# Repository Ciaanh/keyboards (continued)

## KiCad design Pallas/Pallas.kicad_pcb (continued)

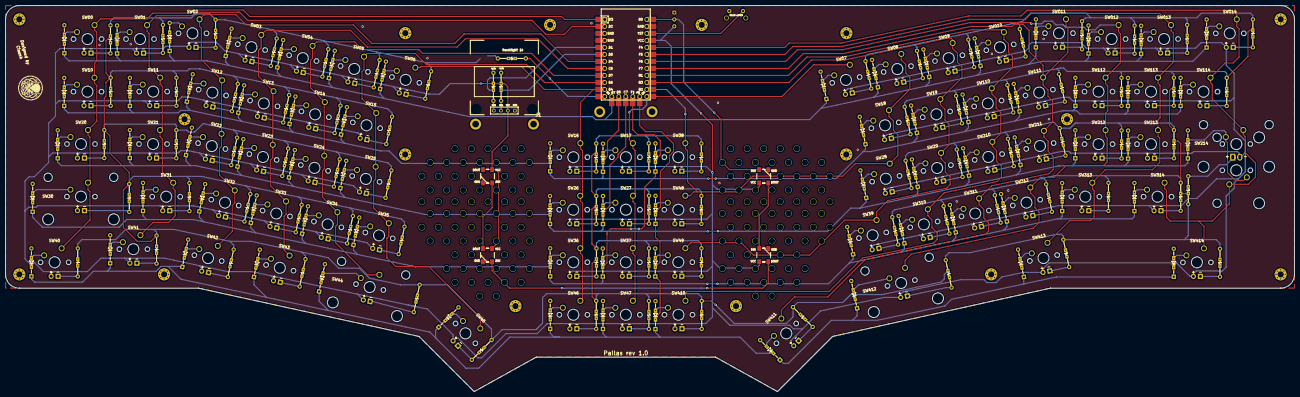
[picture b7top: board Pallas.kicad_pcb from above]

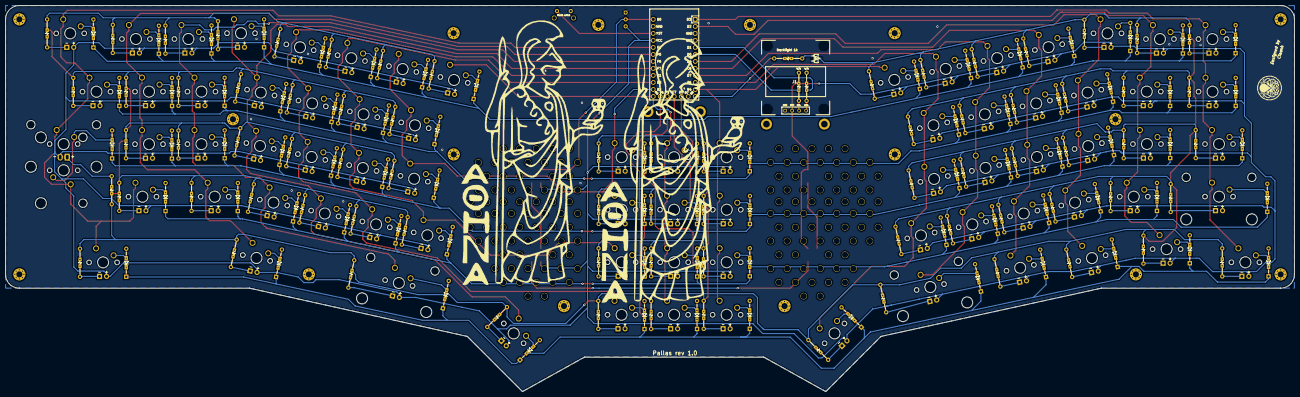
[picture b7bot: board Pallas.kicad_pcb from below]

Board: 2 copper layers, 467.5 x 140.0 mm, 262 parts (3 on the bottom side), 182 nets.

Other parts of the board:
DecorationHoleTop1, DecorationHoleTop2: DecorationHole
LogoBase1: LOGO; athena
LogoBaseMiddleTop: LOGO; Ciaanh_signature
LogoMiddle2: LOGO; athena
MountBaseMiddleTop0, MountBaseMiddleTop2, MountBaseMiddleTop3, MountBaseMiddleTop4, MountBaseMiddleTop5, MountBaseMiddleTop6, MountBaseMiddleTop7, MountBaseMiddleTop8, MountBaseMiddleTop9, MountBaseMiddleTop10, MountBaseMiddleTop11, MountBaseMiddleTop12, MountBaseMiddleTop13, MountBaseMiddleTop14, MountBaseMiddleTop15, MountBaseMiddleTop15#2: MountingHole; MountingHole_2.2mm_M2_Pad_Via
MountForMiddle1: HOLE; MountingHole_2.4mm_M2_Pad
MountMiddle1, MountMiddle2, MountMiddle3: HOLE; MountingHole_2.4mm_M2_Pad

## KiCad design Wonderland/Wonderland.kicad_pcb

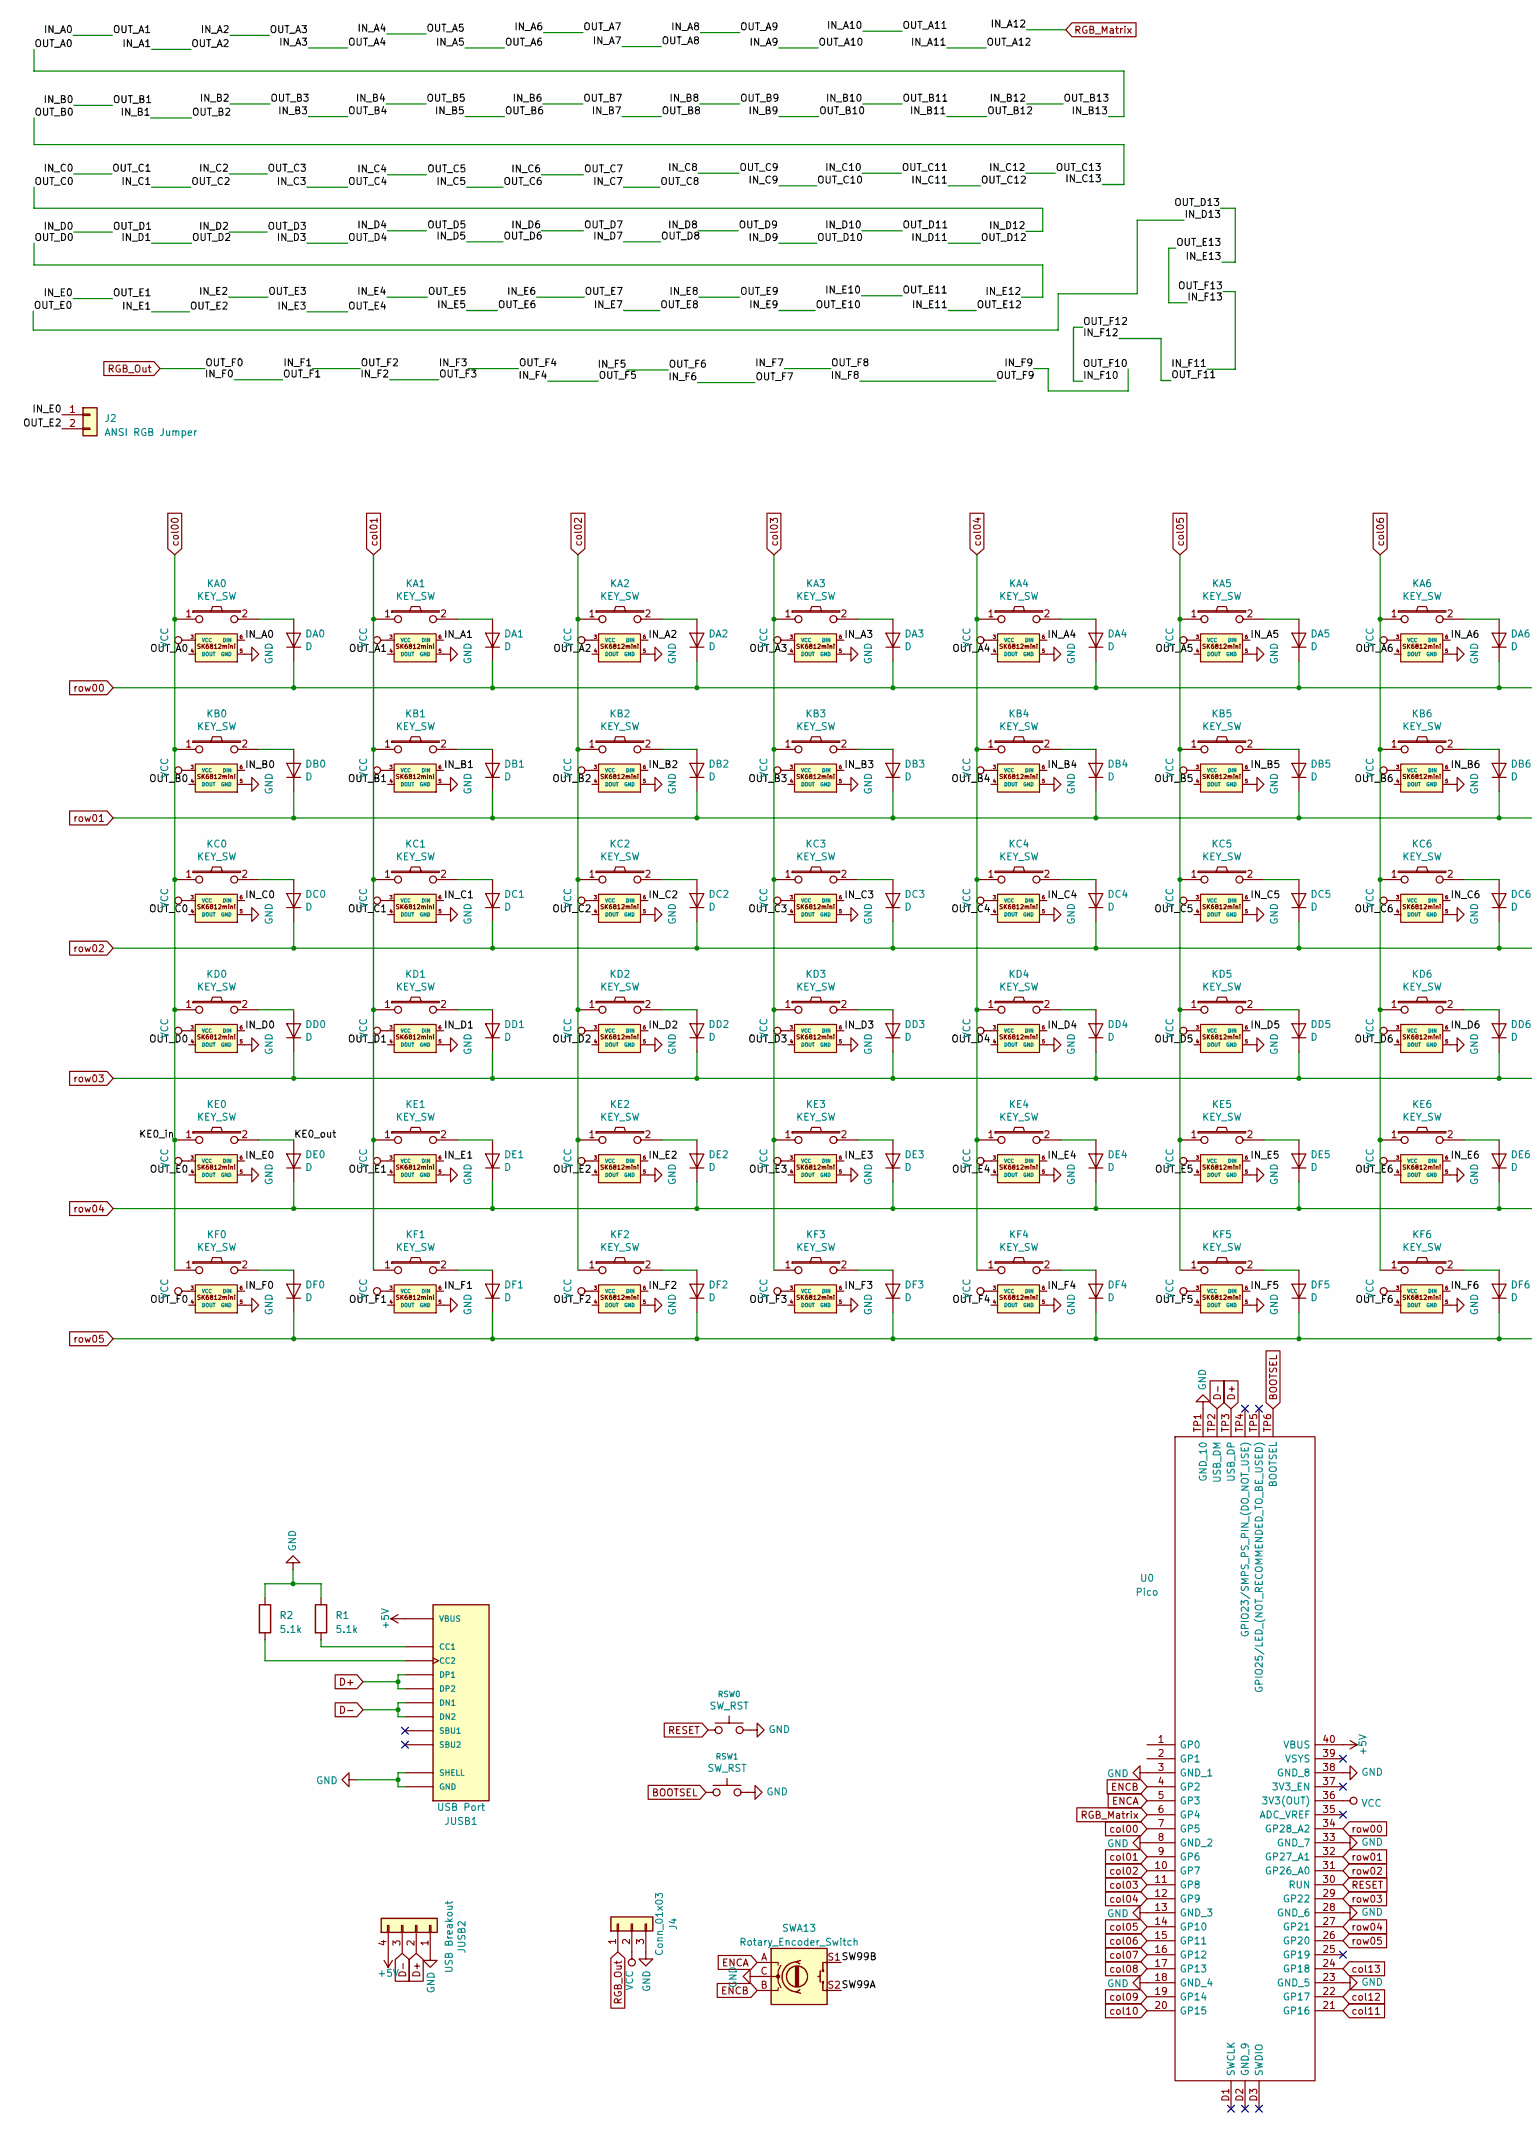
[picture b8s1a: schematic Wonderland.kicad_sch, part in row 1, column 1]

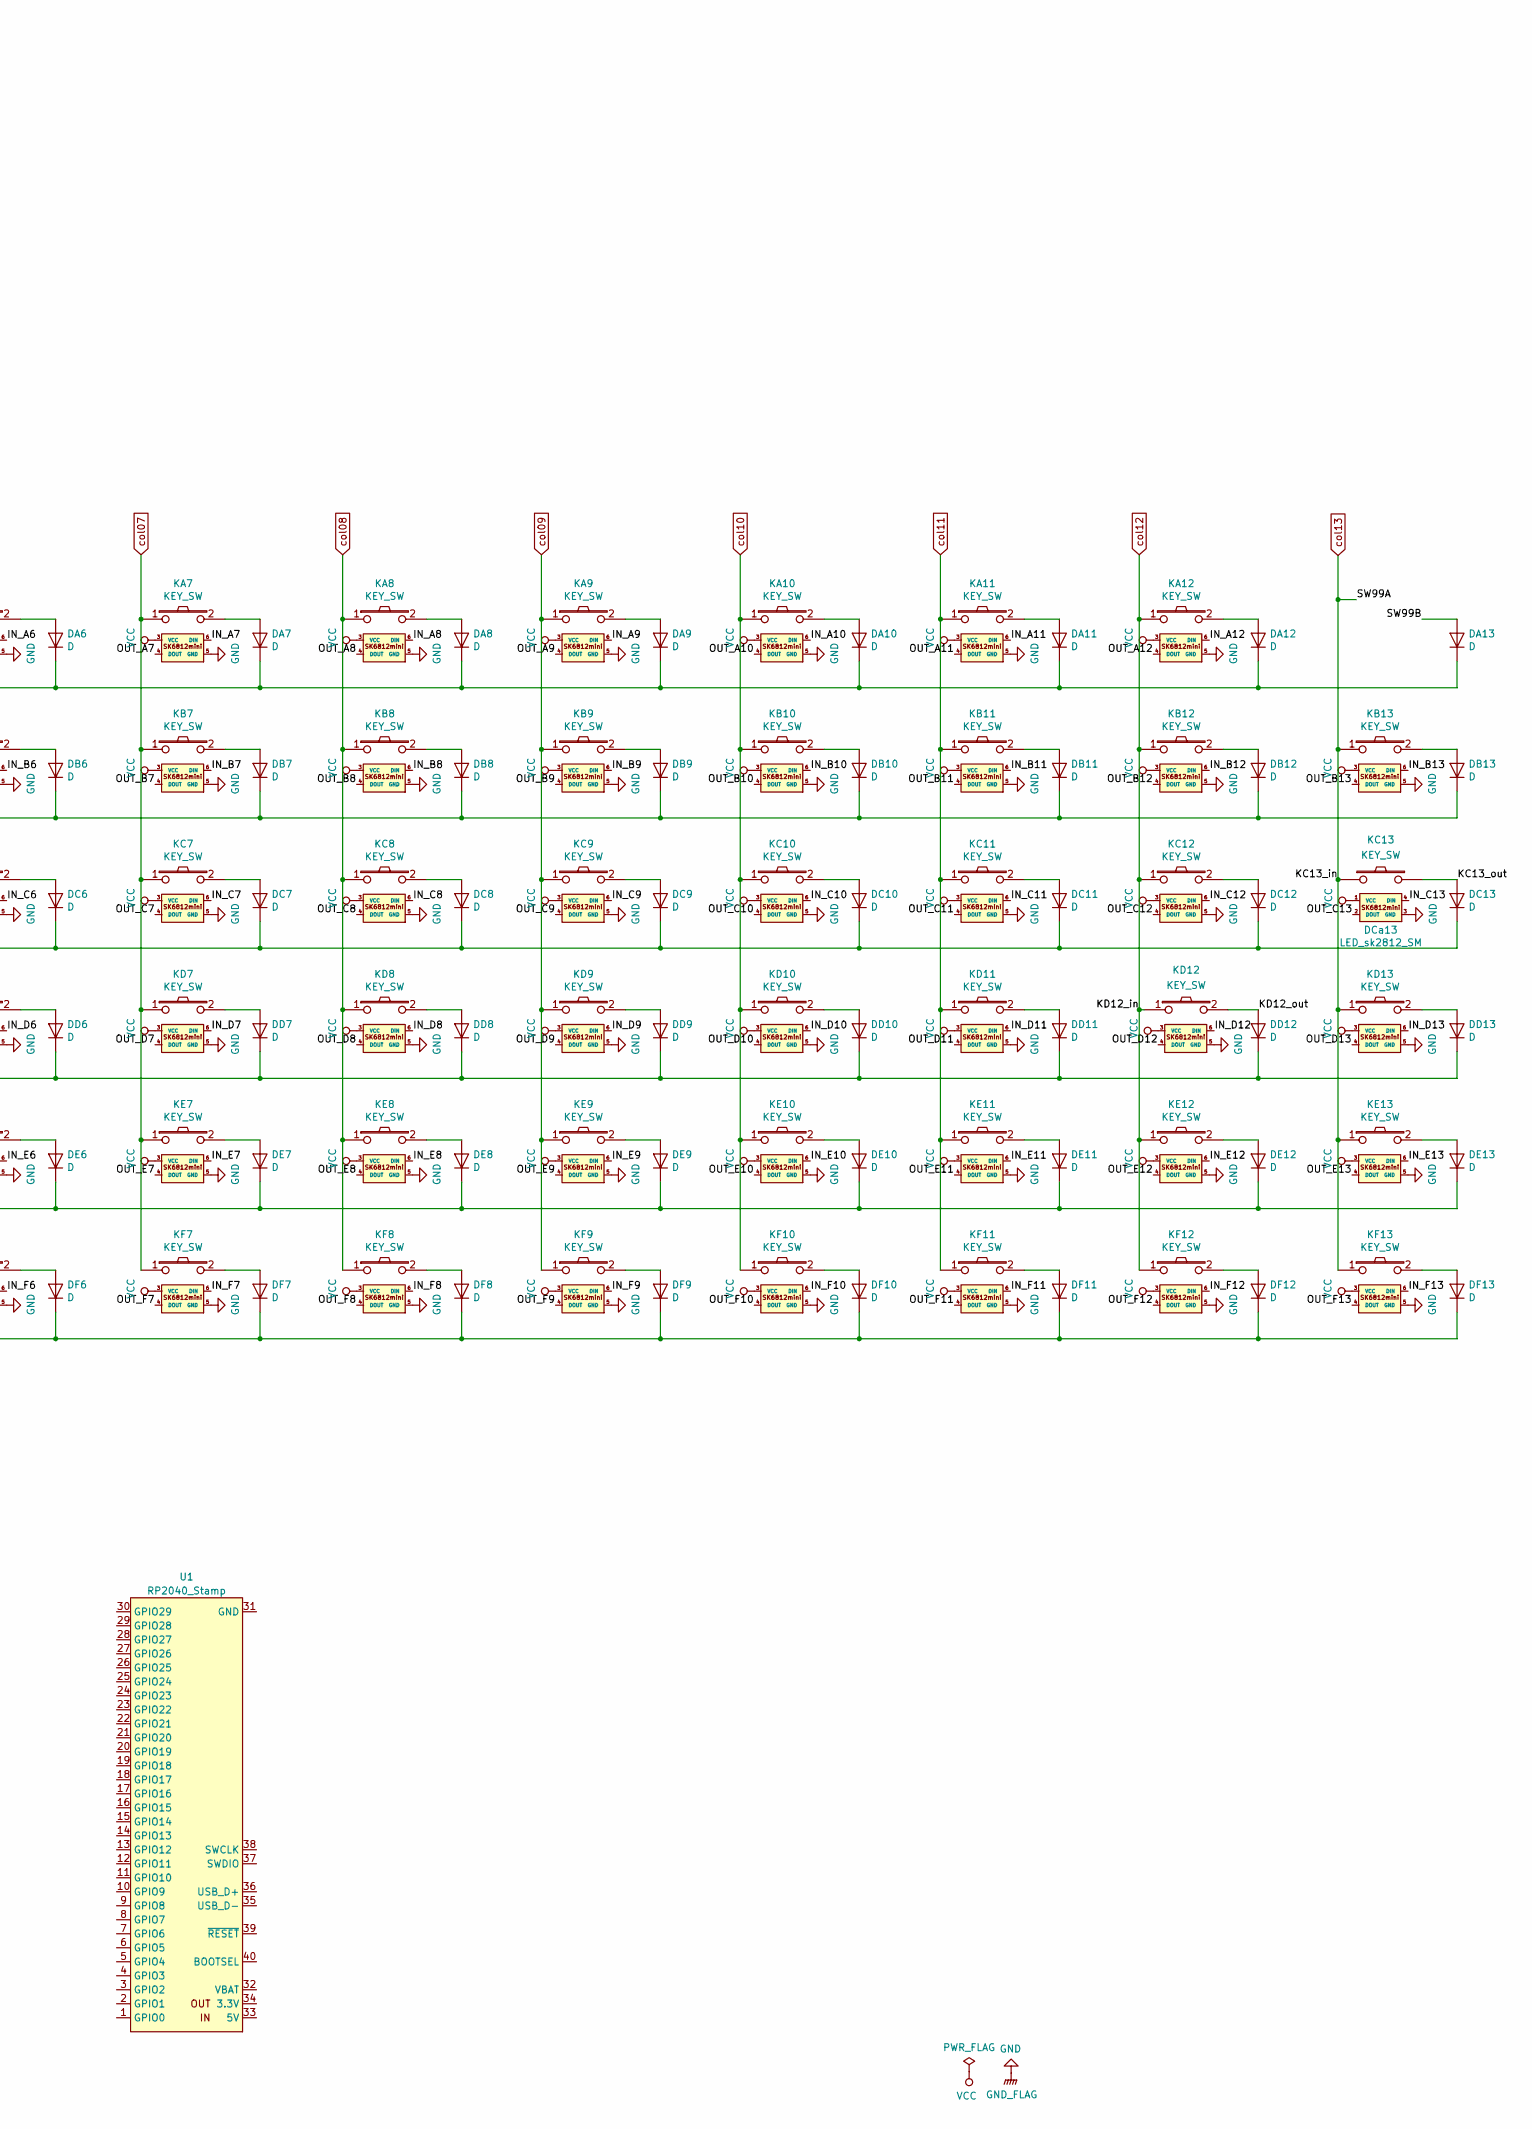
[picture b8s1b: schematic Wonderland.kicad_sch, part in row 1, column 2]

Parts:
DA0, DA1, DA2, DA3, DA4, DA5, DA6, DA7, DA8, DA9, DA10, DA11, DA12, DA13: D; Diode_THT
DB0, DB1, DB2, DB3, DB4, DB5, DB6, DB7, DB8, DB9, DB10, DB11, DB12, DB13: D; Diode_THT
DC0, DC1, DC2, DC3, DC4, DC5, DC6, DC7, DC8, DC9, DC10, DC11, DC12, DC13: D; Diode_THT
DCa13: LED_sk2812_SM; SK6812-MINI-E_back
DD0, DD1, DD2, DD3, DD4, DD5, DD6, DD7, DD8, DD9, DD10, DD11, DD12, DD13: D; Diode_THT
DE0, DE1, DE2, DE3, DE4, DE5, DE6, DE7, DE8, DE9, DE10, DE11, DE12, DE13: D; Diode_THT
DF0, DF1, DF2, DF3, DF4, DF5, DF6, DF7, DF8, DF9, DF10, DF11, DF12, DF13: D; Diode_THT
J2: ANSI RGB Jumper; SolderJumper
J4: Conn_01x03; conn_3pins
JUSB1: USB Port; GCT_USB4085-GF-A_REVA4; PARTREV A4
JUSB2: USB Breakout; conn_4pins
KA0, KA1, KA2, KA3, KA4, KA5, KA6, KA7, KA8, KA9, KA10, KA11, KA12: KEY_SW; SW_Cherry_MX_1.00u_SK6812MINI-E_Hotswap
KB0, KB1, KB2, KB3, KB4, KB5, KB6, KB7, KB8, KB9, KB10, KB11, KB12: KEY_SW; SW_Cherry_MX_1.00u_SK6812MINI-E_Hotswap
KB13: KEY_SW; SW_Cherry_MX_2.00u_SK6812MINI-E_Hotswap
KC0: KEY_SW; SW_Cherry_MX_1.50u_SK6812MINI-E_Hotswap
KC1, KC2, KC3, KC4, KC5, KC6, KC7, KC8, KC9, KC10, KC11, KC12: KEY_SW; SW_Cherry_MX_1.00u_SK6812MINI-E_Hotswap
KC13: KEY_SW; SW_Cherry_MX_2.25u_ISO_Hotswap
KD0: KEY_SW; SW_Cherry_MX_1.75u_SK6812MINI-E_Hotswap
KD1, KD2, KD3, KD4, KD5, KD6, KD7, KD8, KD9, KD10, KD11, KD12, KD13: KEY_SW; SW_Cherry_MX_1.00u_SK6812MINI-E_Hotswap
KE0: KEY_SW; SW_Cherry_MX_1.25u_SK6812MINI-E_Hotswap
KE1, KE2, KE3, KE4, KE5, KE6, KE7, KE8, KE9, KE10, KE11, KE13: KEY_SW; SW_Cherry_MX_1.00u_SK6812MINI-E_Hotswap
KE12: KEY_SW; SW_Cherry_MX_1.75u_SK6812MINI-E_Hotswap
KF0, KF1, KF2, KF3, KF6, KF7, KF8, KF9, KF10, KF11, KF12, KF13: KEY_SW; SW_Cherry_MX_1.00u_SK6812MINI-E_Hotswap
KF4: KEY_SW; SW_Cherry_MX_2.25u_SK6812MINI-E_Hotswap_Reversed
KF5: KEY_SW; SW_Cherry_MX_2.75u_SK6812MINI-E_Hotswap_Reversed
R1, R2: 5.1k; Resistors_THT
RSW0, RSW1: SW_RST
SWA13: Rotary_Encoder_Switch; RotaryEncoder_EC11-Switch_Horizontal_H15mm
U0: Pico; RPi_Pico_TH; Manufacturer_Part_Number PICO
U1: RP2040_Stamp; RP2040_Stamp_THT

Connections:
+5V: JUSB1.A4 (VBUS), JUSB1.A9 (VBUS), JUSB1.B4 (VBUS), JUSB1.B9 (VBUS), JUSB2.4, U0.40 (VBUS)
/IN_A0: KA0.6 (DIN), KA1.4 (DOUT)
/IN_A1: KA1.6 (DIN), KA2.4 (DOUT)
/IN_A2: KA2.6 (DIN), KA3.4 (DOUT)
/IN_A3: KA3.6 (DIN), KA4.4 (DOUT)
/IN_A4: KA4.6 (DIN), KA5.4 (DOUT)
/IN_A5: KA5.6 (DIN), KA6.4 (DOUT)
/IN_A6: KA6.6 (DIN), KA7.4 (DOUT)
/IN_A7: KA7.6 (DIN), KA8.4 (DOUT)
/IN_A8: KA8.6 (DIN), KA9.4 (DOUT)
/IN_A9: KA9.6 (DIN), KA10.4 (DOUT)
/IN_A10: KA10.6 (DIN), KA11.4 (DOUT)
/IN_A11: KA11.6 (DIN), KA12.4 (DOUT)
/IN_B0: KB0.6 (DIN), KB1.4 (DOUT)
/IN_B1: KB1.6 (DIN), KB2.4 (DOUT)
/IN_B2: KB2.6 (DIN), KB3.4 (DOUT)
/IN_B3: KB3.6 (DIN), KB4.4 (DOUT)
/IN_B4: KB4.6 (DIN), KB5.4 (DOUT)
/IN_B5: KB5.6 (DIN), KB6.4 (DOUT)
/IN_B6: KB6.6 (DIN), KB7.4 (DOUT)
/IN_B7: KB7.6 (DIN), KB8.4 (DOUT)
/IN_B8: KB8.6 (DIN), KB9.4 (DOUT)
/IN_B9: KB9.6 (DIN), KB10.4 (DOUT)
/IN_B10: KB10.6 (DIN), KB11.4 (DOUT)
/IN_B11: KB11.6 (DIN), KB12.4 (DOUT)
/IN_B12: KB12.6 (DIN), KB13.4 (DOUT)
/IN_B13: KA0.4 (DOUT), KB13.6 (DIN)
/IN_C0: KC0.6 (DIN), KC1.4 (DOUT)
/IN_C1: KC1.6 (DIN), KC2.4 (DOUT)
/IN_C2: KC2.6 (DIN), KC3.4 (DOUT)
/IN_C3: KC3.6 (DIN), KC4.4 (DOUT)
/IN_C4: KC4.6 (DIN), KC5.4 (DOUT)
/IN_C5: KC5.6 (DIN), KC6.4 (DOUT)
/IN_C6: KC6.6 (DIN), KC7.4 (DOUT)
/IN_C7: KC7.6 (DIN), KC8.4 (DOUT)
/IN_C8: KC8.6 (DIN), KC9.4 (DOUT)
/IN_C9: KC9.6 (DIN), KC10.4 (DOUT)
/IN_C10: KC10.6 (DIN), KC11.4 (DOUT)
/IN_C11: KC11.6 (DIN), KC12.4 (DOUT)
/IN_C12: DCa13.2 (DOUT), KC12.6 (DIN)
/IN_C13: DCa13.4 (DIN), KB0.4 (DOUT)
/IN_D0: KD0.6 (DIN), KD1.4 (DOUT)
/IN_D1: KD1.6 (DIN), KD2.4 (DOUT)
/IN_D2: KD2.6 (DIN), KD3.4 (DOUT)
/IN_D3: KD3.6 (DIN), KD4.4 (DOUT)
/IN_D4: KD4.6 (DIN), KD5.4 (DOUT)
/IN_D5: KD5.6 (DIN), KD6.4 (DOUT)
/IN_D6: KD6.6 (DIN), KD7.4 (DOUT)
/IN_D7: KD7.6 (DIN), KD8.4 (DOUT)
/IN_D8: KD8.6 (DIN), KD9.4 (DOUT)
/IN_D9: KD9.6 (DIN), KD10.4 (DOUT)
/IN_D10: KD10.6 (DIN), KD11.4 (DOUT)
/IN_D11: KD11.6 (DIN), KD12.4 (DOUT)
/IN_D12: KC0.4 (DOUT), KD12.6 (DIN)
/IN_D13: KD13.6 (DIN), KE0.4 (DOUT)
/IN_E0: J2.1, KE0.6 (DIN), KE1.4 (DOUT)
/IN_E1: J2.2, KE1.6 (DIN), KE2.4 (DOUT)
/IN_E2: KE2.6 (DIN), KE3.4 (DOUT)
/IN_E3: KE3.6 (DIN), KE4.4 (DOUT)
/IN_E4: KE4.6 (DIN), KE5.4 (DOUT)
/IN_E5: KE5.6 (DIN), KE6.4 (DOUT)
/IN_E6: KE6.6 (DIN), KE7.4 (DOUT)
/IN_E7: KE7.6 (DIN), KE8.4 (DOUT)
/IN_E8: KE8.6 (DIN), KE9.4 (DOUT)
/IN_E9: KE9.6 (DIN), KE10.4 (DOUT)
/IN_E10: KE10.6 (DIN), KE11.4 (DOUT)
/IN_E11: KE11.6 (DIN), KE12.4 (DOUT)
/IN_E12: KD0.4 (DOUT), KE12.6 (DIN)
/IN_E13: KD13.4 (DOUT), KE13.6 (DIN)
/IN_F0: KF0.6 (DIN), KF1.4 (DOUT)
/IN_F1: KF1.6 (DIN), KF2.4 (DOUT)
/IN_F2: KF2.6 (DIN), KF3.4 (DOUT)
/IN_F3: KF3.6 (DIN), KF4.4 (DOUT)
/IN_F4: KF4.6 (DIN), KF5.4 (DOUT)
/IN_F5: KF5.6 (DIN), KF6.4 (DOUT)
/IN_F6: KF6.6 (DIN), KF7.4 (DOUT)
/IN_F7: KF7.6 (DIN), KF8.4 (DOUT)
/IN_F8: KF8.6 (DIN), KF9.4 (DOUT)
/IN_F9: KF9.6 (DIN), KF10.4 (DOUT)
/IN_F10: KF10.6 (DIN), KF12.4 (DOUT)
/IN_F11: KF11.6 (DIN), KF13.4 (DOUT)
/IN_F12: KF11.4 (DOUT), KF12.6 (DIN)
/IN_F13: KE13.4 (DOUT), KF13.6 (DIN)
/KC13_out: DC13.2 (A), KC13.2
/KD12_out: DD12.2 (A), KD12.2
/KE0_out: DE0.2 (A), KE0.2
/SW99B: DA13.2 (A), SWA13.S1
BOOTSEL: RSW1.1, U0.TP6 (BOOTSEL)
D+: JUSB1.A6 (DP1), JUSB1.B6 (DP2), JUSB2.2, U0.TP3 (USB_DP)
D-: JUSB1.A7 (DN1), JUSB1.B7 (DN2), JUSB2.3, U0.TP2 (USB_DM)
ENCA: SWA13.A, U0.5 (GP3)
ENCB: SWA13.B, U0.4 (GP2)
GND: DCa13.3 (GND), J4.3, JUSB1.A1 (GND), JUSB1.A12 (GND), JUSB1.B1 (GND), JUSB1.B12 (GND), JUSB1.P1 (SHELL), JUSB1.P2 (SHELL), JUSB1.P3 (SHELL), JUSB1.P4 (SHELL), JUSB2.1, KA0.5 (GND), KA1.5 (GND), KA2.5 (GND), KA3.5 (GND), KA4.5 (GND), KA5.5 (GND), KA6.5 (GND), KA7.5 (GND), KA8.5 (GND), KA9.5 (GND), KA10.5 (GND), KA11.5 (GND), KA12.5 (GND), KB0.5 (GND), KB1.5 (GND), KB2.5 (GND), KB3.5 (GND), KB4.5 (GND), KB5.5 (GND), KB6.5 (GND), KB7.5 (GND), KB8.5 (GND), KB9.5 (GND), KB10.5 (GND), KB11.5 (GND), KB12.5 (GND), KB13.5 (GND), KC0.5 (GND), KC1.5 (GND), KC2.5 (GND), KC3.5 (GND), KC4.5 (GND), KC5.5 (GND), KC6.5 (GND), KC7.5 (GND), KC8.5 (GND), KC9.5 (GND), KC10.5 (GND), KC11.5 (GND), KC12.5 (GND), KD0.5 (GND), KD1.5 (GND), KD2.5 (GND), KD3.5 (GND), KD4.5 (GND), KD5.5 (GND), KD6.5 (GND), KD7.5 (GND), KD8.5 (GND), KD9.5 (GND), KD10.5 (GND), KD11.5 (GND), KD12.5 (GND), KD13.5 (GND), KE0.5 (GND), KE1.5 (GND), KE2.5 (GND), KE3.5 (GND), KE4.5 (GND), KE5.5 (GND), KE6.5 (GND), KE7.5 (GND), KE8.5 (GND), KE9.5 (GND), KE10.5 (GND), KE11.5 (GND), KE12.5 (GND), KE13.5 (GND), KF0.5 (GND), KF1.5 (GND), KF2.5 (GND), KF3.5 (GND), KF4.5 (GND), KF5.5 (GND), KF6.5 (GND), KF7.5 (GND), KF8.5 (GND), KF9.5 (GND), KF10.5 (GND), KF11.5 (GND), KF12.5 (GND), KF13.5 (GND), R1.1, R2.1, RSW0.2, RSW1.2, SWA13.C, U0.3 (GND_1), U0.8 (GND_2), U0.13 (GND_3), U0.18 (GND_4), U0.23 (GND_5), U0.28 (GND_6), U0.33 (GND_7), U0.38 (GND_8), U0.TP1 (GND_10)
unnamed: DA0.2 (A), KA0.2
unnamed: DA1.2 (A), KA1.2
unnamed: DA2.2 (A), KA2.2
unnamed: DA3.2 (A), KA3.2
unnamed: DA4.2 (A), KA4.2
unnamed: DA5.2 (A), KA5.2
unnamed: DA6.2 (A), KA6.2
unnamed: DA7.2 (A), KA7.2
unnamed: DA8.2 (A), KA8.2
unnamed: DA9.2 (A), KA9.2
unnamed: DA10.2 (A), KA10.2
unnamed: DA11.2 (A), KA11.2
unnamed: DA12.2 (A), KA12.2
unnamed: DB0.2 (A), KB0.2
unnamed: DB1.2 (A), KB1.2
unnamed: DB2.2 (A), KB2.2
unnamed: DB3.2 (A), KB3.2
unnamed: DB4.2 (A), KB4.2
unnamed: DB5.2 (A), KB5.2
unnamed: DB6.2 (A), KB6.2
unnamed: DB7.2 (A), KB7.2
unnamed: DB8.2 (A), KB8.2
unnamed: DB9.2 (A), KB9.2
unnamed: DB10.2 (A), KB10.2
unnamed: DB11.2 (A), KB11.2
unnamed: DB12.2 (A), KB12.2
unnamed: DB13.2 (A), KB13.2
unnamed: DC0.2 (A), KC0.2
unnamed: DC1.2 (A), KC1.2
unnamed: DC2.2 (A), KC2.2
unnamed: DC3.2 (A), KC3.2
unnamed: DC4.2 (A), KC4.2
unnamed: DC5.2 (A), KC5.2
unnamed: DC6.2 (A), KC6.2
unnamed: DC7.2 (A), KC7.2
unnamed: DC8.2 (A), KC8.2
unnamed: DC9.2 (A), KC9.2
unnamed: DC10.2 (A), KC10.2
unnamed: DC11.2 (A), KC11.2
unnamed: DC12.2 (A), KC12.2
unnamed: DD0.2 (A), KD0.2
unnamed: DD1.2 (A), KD1.2
unnamed: DD2.2 (A), KD2.2
unnamed: DD3.2 (A), KD3.2
unnamed: DD4.2 (A), KD4.2
unnamed: DD5.2 (A), KD5.2
unnamed: DD6.2 (A), KD6.2
unnamed: DD7.2 (A), KD7.2
unnamed: DD8.2 (A), KD8.2
unnamed: DD9.2 (A), KD9.2
unnamed: DD10.2 (A), KD10.2
unnamed: DD11.2 (A), KD11.2
unnamed: DD13.2 (A), KD13.2
unnamed: DE1.2 (A), KE1.2
unnamed: DE2.2 (A), KE2.2
unnamed: DE3.2 (A), KE3.2
unnamed: DE4.2 (A), KE4.2
unnamed: DE5.2 (A), KE5.2
unnamed: DE6.2 (A), KE6.2
unnamed: DE7.2 (A), KE7.2
unnamed: DE8.2 (A), KE8.2
unnamed: DE9.2 (A), KE9.2
unnamed: DE10.2 (A), KE10.2
unnamed: DE11.2 (A), KE11.2
unnamed: DE12.2 (A), KE12.2
unnamed: DE13.2 (A), KE13.2
unnamed: DF0.2 (A), KF0.2
unnamed: DF1.2 (A), KF1.2
unnamed: DF2.2 (A), KF2.2
unnamed: DF3.2 (A), KF3.2
unnamed: DF4.2 (A), KF4.2
unnamed: DF5.2 (A), KF5.2
unnamed: DF6.2 (A), KF6.2
unnamed: DF7.2 (A), KF7.2
unnamed: DF8.2 (A), KF8.2
unnamed: DF9.2 (A), KF9.2
unnamed: DF10.2 (A), KF10.2
unnamed: DF11.2 (A), KF11.2
unnamed: DF12.2 (A), KF12.2
unnamed: DF13.2 (A), KF13.2
unnamed: JUSB1.A5 (CC1), R1.2
unnamed: JUSB1.B5 (CC2), R2.2
RESET: RSW0.1, U0.30 (RUN)
RGB_Matrix: KA12.6 (DIN), U0.6 (GP4)
RGB_Out: J4.1, KF0.4 (DOUT)
VCC: DCa13.1 (VCC), J4.2, KA0.3 (VCC), KA1.3 (VCC), KA2.3 (VCC), KA3.3 (VCC), KA4.3 (VCC), KA5.3 (VCC), KA6.3 (VCC), KA7.3 (VCC), KA8.3 (VCC), KA9.3 (VCC), KA10.3 (VCC), KA11.3 (VCC), KA12.3 (VCC), KB0.3 (VCC), KB1.3 (VCC), KB2.3 (VCC), KB3.3 (VCC), KB4.3 (VCC), KB5.3 (VCC), KB6.3 (VCC), KB7.3 (VCC), KB8.3 (VCC), KB9.3 (VCC), KB10.3 (VCC), KB11.3 (VCC), KB12.3 (VCC), KB13.3 (VCC), KC0.3 (VCC), KC1.3 (VCC), KC2.3 (VCC), KC3.3 (VCC), KC4.3 (VCC), KC5.3 (VCC), KC6.3 (VCC), KC7.3 (VCC), KC8.3 (VCC), KC9.3 (VCC), KC10.3 (VCC), KC11.3 (VCC), KC12.3 (VCC), KD0.3 (VCC), KD1.3 (VCC), KD2.3 (VCC), KD3.3 (VCC), KD4.3 (VCC), KD5.3 (VCC), KD6.3 (VCC), KD7.3 (VCC), KD8.3 (VCC), KD9.3 (VCC), KD10.3 (VCC), KD11.3 (VCC), KD12.3 (VCC), KD13.3 (VCC), KE0.3 (VCC), KE1.3 (VCC), KE2.3 (VCC), KE3.3 (VCC), KE4.3 (VCC), KE5.3 (VCC), KE6.3 (VCC), KE7.3 (VCC), KE8.3 (VCC), KE9.3 (VCC), KE10.3 (VCC), KE11.3 (VCC), KE12.3 (VCC), KE13.3 (VCC), KF0.3 (VCC), KF1.3 (VCC), KF2.3 (VCC), KF3.3 (VCC), KF4.3 (VCC), KF5.3 (VCC), KF6.3 (VCC), KF7.3 (VCC), KF8.3 (VCC), KF9.3 (VCC), KF10.3 (VCC), KF11.3 (VCC), KF12.3 (VCC), KF13.3 (VCC), U0.36 (3V3(OUT))
col00: KA0.1, KB0.1, KC0.1, KD0.1, KE0.1, KF0.1, U0.7 (GP5)
col01: KA1.1, KB1.1, KC1.1, KD1.1, KE1.1, KF1.1, U0.9 (GP6)
col02: KA2.1, KB2.1, KC2.1, KD2.1, KE2.1, KF2.1, U0.10 (GP7)
col03: KA3.1, KB3.1, KC3.1, KD3.1, KE3.1, KF3.1, U0.11 (GP8)
col04: KA4.1, KB4.1, KC4.1, KD4.1, KE4.1, KF4.1, U0.12 (GP9)
col05: KA5.1, KB5.1, KC5.1, KD5.1, KE5.1, KF5.1, U0.14 (GP10)
col06: KA6.1, KB6.1, KC6.1, KD6.1, KE6.1, KF6.1, U0.15 (GP11)
col07: KA7.1, KB7.1, KC7.1, KD7.1, KE7.1, KF7.1, U0.16 (GP12)
col08: KA8.1, KB8.1, KC8.1, KD8.1, KE8.1, KF8.1, U0.17 (GP13)
col09: KA9.1, KB9.1, KC9.1, KD9.1, KE9.1, KF9.1, U0.19 (GP14)
col10: KA10.1, KB10.1, KC10.1, KD10.1, KE10.1, KF10.1, U0.20 (GP15)
col11: KA11.1, KB11.1, KC11.1, KD11.1, KE11.1, KF11.1, U0.21 (GP16)
col12: KA12.1, KB12.1, KC12.1, KD12.1, KE12.1, KF12.1, U0.22 (GP17)
col13: KB13.1, KC13.1, KD13.1, KE13.1, KF13.1, SWA13.S2, U0.24 (GP18)
row00: DA0.1 (K), DA1.1 (K), DA2.1 (K), DA3.1 (K), DA4.1 (K), DA5.1 (K), DA6.1 (K), DA7.1 (K), DA8.1 (K), DA9.1 (K), DA10.1 (K), DA11.1 (K), DA12.1 (K), DA13.1 (K), U0.34 (GP28_A2)
row01: DB0.1 (K), DB1.1 (K), DB2.1 (K), DB3.1 (K), DB4.1 (K), DB5.1 (K), DB6.1 (K), DB7.1 (K), DB8.1 (K), DB9.1 (K), DB10.1 (K), DB11.1 (K), DB12.1 (K), DB13.1 (K), U0.32 (GP27_A1)
row02: DC0.1 (K), DC1.1 (K), DC2.1 (K), DC3.1 (K), DC4.1 (K), DC5.1 (K), DC6.1 (K), DC7.1 (K), DC8.1 (K), DC9.1 (K), DC10.1 (K), DC11.1 (K), DC12.1 (K), DC13.1 (K), U0.31 (GP26_A0)
row03: DD0.1 (K), DD1.1 (K), DD2.1 (K), DD3.1 (K), DD4.1 (K), DD5.1 (K), DD6.1 (K), DD7.1 (K), DD8.1 (K), DD9.1 (K), DD10.1 (K), DD11.1 (K), DD12.1 (K), DD13.1 (K), U0.29 (GP22)
row04: DE0.1 (K), DE1.1 (K), DE2.1 (K), DE3.1 (K), DE4.1 (K), DE5.1 (K), DE6.1 (K), DE7.1 (K), DE8.1 (K), DE9.1 (K), DE10.1 (K), DE11.1 (K), DE12.1 (K), DE13.1 (K), U0.27 (GP21)
row05: DF0.1 (K), DF1.1 (K), DF2.1 (K), DF3.1 (K), DF4.1 (K), DF5.1 (K), DF6.1 (K), DF7.1 (K), DF8.1 (K), DF9.1 (K), DF10.1 (K), DF11.1 (K), DF12.1 (K), DF13.1 (K), U0.26 (GP20)

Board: 2 copper layers, 180 parts (4 on the bottom side), 199 nets, no tracks yet.

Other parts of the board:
LogoMiddleBack: LOGO; Wave_mask

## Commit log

2020-06-01 add readme
2020-06-01 Consolidate symbol and fp libraries
2020-07-03 update pcb for footprint stabs
2020-07-04 rev 0.2 fix diode an res position with stabs
2020-07-05 Add decorations holes
2020-07-05 Fix label switch label with stabs
2020-07-05 generate rev 0.2 pcbs
2020-07-05 Generate gerber files
2020-09-09 Fix issue with label design by
2020-12-27 Review diode and resistor position with stabs
2021-01-05 update RGB led footprint and route
2021-01-05 clean routes
2021-01-05 New routes
2021-01-07 Pallas rev 0.3
2021-01-07 Update gerber
2021-01-16 Add image
2021-01-16 Edit readme
2021-01-16 Fix indent for list
2021-01-21 Remove zips
2021-01-21 init project
2021-01-21 review
2021-01-23 Split modules into seperate projects
2021-01-24 add link pcb
2021-02-05 fix mosfet footprint
2021-02-07 Edit oled footprint
2021-02-07 link bridge
2021-02-15 improve link
2021-02-15 add hotswap footprint
2021-02-15 add reviung as ref for kanagawa
2021-02-15 add test
2021-02-25 Test project
2021-03-11 add potential layout
2021-08-23 edit layout
2021-08-28 refs
2021-08-28 Create project Kanagawa with layout
2021-09-02 Add footprints
2021-09-02 Begin placing footprints
2021-09-03 update footprint
2021-09-04 prepare pcb layout
2021-09-04 test footprint
2021-09-04 update pcb
2021-09-04 begin routes
2021-09-06 wip pcb
2021-09-07 wip routing
2021-09-09 rework routing
2021-09-12 Kanagawa routing
2021-09-15 edit kanagawa
2021-09-21 Add revisions
2021-09-21 remove rev 2 generated
2021-09-21 edit rev2
2021-09-21 clean project
2021-10-02 clean revisions
2021-10-02 routing rev1
2021-10-23 reviewe kanagawa rev1
2021-10-24 edit arc for edge cut in script
2021-10-28 update script pcb generation
2021-10-30 change R D footprint
2021-10-30 rev1 routing done
2021-11-11 edit pcb
2021-11-29 rework rev1 from fusion layout
2021-12-01 review board
2021-12-18 review board edges
2022-01-10 review PCB
2022-01-10 generate kanagawa gerber
2022-01-11 add rev1_rgb
2022-01-23 Add new case stl
2022-01-30 re route pcbs
2022-02-07 release 1.0
2022-02-07 clean pallas
2022-02-07 Clean after merge
2022-06-05 add empty talk files
2022-06-13 Add talk images
2022-06-13 Update pictures
2022-06-13 Update talk and picture
2022-06-13 change talk file name to readme
2022-06-13 define images
2022-06-17 update prez
2022-06-17 review article
2022-06-18 wip rgb
2022-06-18 Separate iso and ansi format
2022-06-24 restart RGB
2022-07-05 edit kanagawa rgb
2022-07-06 Begin routing ANSI
2022-07-11 edit usb breakout
2022-07-17 rework rev2 kanagawa
2022-07-29 add stamp version
2022-08-04 edit stamp version
2022-08-06 work on rev2 changes
2022-09-22 Update symbol
2022-12-11 add v2 H
2022-12-11 edit iso H
2022-12-11 H version
2022-12-12 iso H
2022-12-12 gerber H
2023-01-29 adjust kanagawa rev2 pcbs
2023-01-29 merge
2023-02-08 remove zip
2023-03-10 edit Kanagawa PCB
2023-04-29 add case files
2023-05-08 update kanagawa rev2.1 case files
2023-05-08 fix files ref
2023-07-01 add uf2 firmware
2023-07-01 Add Kanagawa build guide
2023-07-01 Fix build guide images
2023-07-01 Add link
2024-01-09 Edit excel led matrix
2024-01-09 edit matrix file
2024-01-10 Add wonderland
2024-01-14 update wonderland routes
2024-01-14 remove backups
2024-01-15 update routes
2024-01-15 edit wonderland routes
2024-01-16 add ref for JLCPCB bom
2024-01-17 edit wonderland + try rp2040
2024-01-17 add refs for mcu
2024-01-17 something changed
2024-01-17 add test board rp2040
2024-01-18 add test board
2024-01-18 add rp2040 minimal & review test board with hardware specs
2024-01-18 review schematics
2024-01-18 edit full pcb
2024-01-19 review schematics wonderland
2024-01-19 update wonderland
2024-01-26 Add Antikythera
2024-01-26 remove backup
2024-01-29 generated PCB
2024-01-29 edit generating script
2024-01-29 create rgb matrix project
2024-02-22 edit
2024-06-22 update talk 2024
2024-06-27 update talk
